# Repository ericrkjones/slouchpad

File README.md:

# slouchpad
A simple joypad for easy assembly in different types of enclosures.  

The joypad is broken into four main components:  
* Left pad, containing one joystick, d-pad, the select button, the menu buttor
* Right pad, containing one joystick, six primary buttons, and the start button
* Two shoulder pads, each containing two buttons.  

Signal List:
* 5 analog signals
* 13 digital signals
* VCC
* GND

## Hardware
Hardware designs are located in the "slouchpad_pcb" directory.
### Components
* Buttons
  * The buttons on all the pads are the Soft Tactile Buttons distributed by Adafruit Industries:
    * [Soft Tactile Button (8mm)](https://www.adafruit.com/products/3101)
  * These buttons provide the feel of a conductive silicone pad button without the expense and difficulty of producing the silicone parts.
* Joysticks
  * Joysticks are Mini 2-Axis Analog Thumbsticks distributed by Adafruit Industries:
    * [Mini 2-Axis Analog Thumbstick](https://www.adafruit.com/products/2765)
  * These joysticks have a feel that is very similar to a PSP joystick, but are available in a through-hole package.  

## License Information
The slouchpad hardware is released under [Creative Commons ShareAlike 4.0 International](https://creativecommons.org/licenses/by-sa/4.0/).  

The Mini Analog Thumbstick part layout was obtained from the [Adafruit-Mini-Analog-Thumbstick-Breakout-PCB](https://github.com/adafruit/Adafruit-Mini-Analog-Thumbstick-Breakout-PCB), designed by Ladyada for Adafruit Industries and released under the [Creative Commons Attribution-ShareAlike license](https://creativecommons.org/licenses/by-sa/3.0/).  Adafruit invests time and resources providing this open source design, please support Adafruit and open-source hardware by purchasing products from Adafruit!

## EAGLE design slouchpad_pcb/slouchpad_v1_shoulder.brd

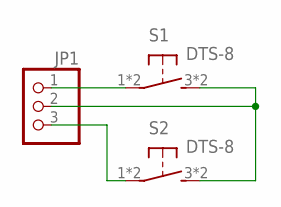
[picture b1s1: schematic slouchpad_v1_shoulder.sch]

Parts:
JP1: PINHD-1X3; 1X03
S1, S2: DTS-8

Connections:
GND: JP1.2, S1.3 (2), S1.4 (2), S2.3 (2), S2.4 (2)
S1: JP1.1, S1.1, S1.2 (1)
S2: JP1.3, S2.1, S2.2 (1)

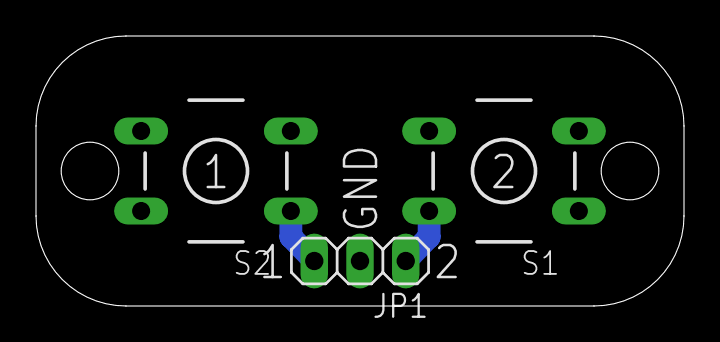
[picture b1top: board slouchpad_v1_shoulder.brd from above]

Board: 2 copper layers, 36.0 x 15.0 mm, 3 parts (0 on the bottom side), 3 nets.

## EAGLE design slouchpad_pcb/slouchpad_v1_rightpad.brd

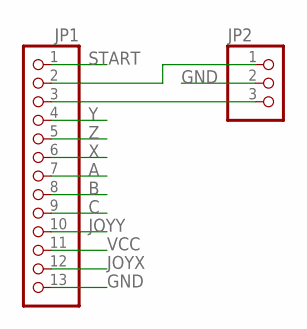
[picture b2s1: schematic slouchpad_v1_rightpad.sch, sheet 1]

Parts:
JP1: PINHD-1X13; 1X13
JP2: PINHD-1X3; 1X03

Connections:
A: JP1.7; also elsewhere on the board
B: JP1.8; also elsewhere on the board
C: JP1.9; also elsewhere on the board
GND: JP1.13, JP2.2; also elsewhere on the board
JOYX: JP1.12; also elsewhere on the board
JOYY: JP1.10; also elsewhere on the board
unnamed: JP1.2, JP2.1
unnamed: JP1.3, JP2.3
START: JP1.1; also elsewhere on the board
VCC: JP1.11; also elsewhere on the board
X: JP1.6; also elsewhere on the board
Y: JP1.4; also elsewhere on the board
Z: JP1.5; also elsewhere on the board

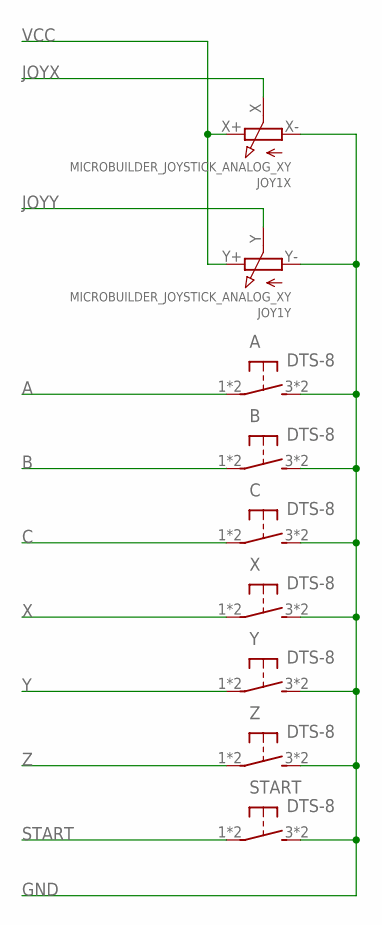
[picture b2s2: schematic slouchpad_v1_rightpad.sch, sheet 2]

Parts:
A: DTS-8
B: DTS-8
C: DTS-8
JOY1: MICROBUILDER_JOYSTICK_ANALOG_XY; MICROBUILDER_JOYSTICK_ANALOG_MINITHM
START: DTS-8
X: DTS-8
Y: DTS-8
Z: DTS-8

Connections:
A: A.1, A.2 (1); also elsewhere on the board
B: B.1, B.2 (1); also elsewhere on the board
C: C.1, C.2 (1); also elsewhere on the board
GND: A.3 (2), A.4 (2), B.3 (2), B.4 (2), C.3 (2), C.4 (2), JOY1.X- (A), JOY1.Y- (A), START.3 (2), START.4 (2), X.3 (2), X.4 (2), Y.3 (2), Y.4 (2), Z.3 (2), Z.4 (2); also elsewhere on the board
JOYX: JOY1.X (S); also elsewhere on the board
JOYY: JOY1.Y (S); also elsewhere on the board
START: START.1, START.2 (1); also elsewhere on the board
VCC: JOY1.X+ (E), JOY1.Y+ (E); also elsewhere on the board
X: X.1, X.2 (1); also elsewhere on the board
Y: Y.1, Y.2 (1); also elsewhere on the board
Z: Z.1, Z.2 (1); also elsewhere on the board

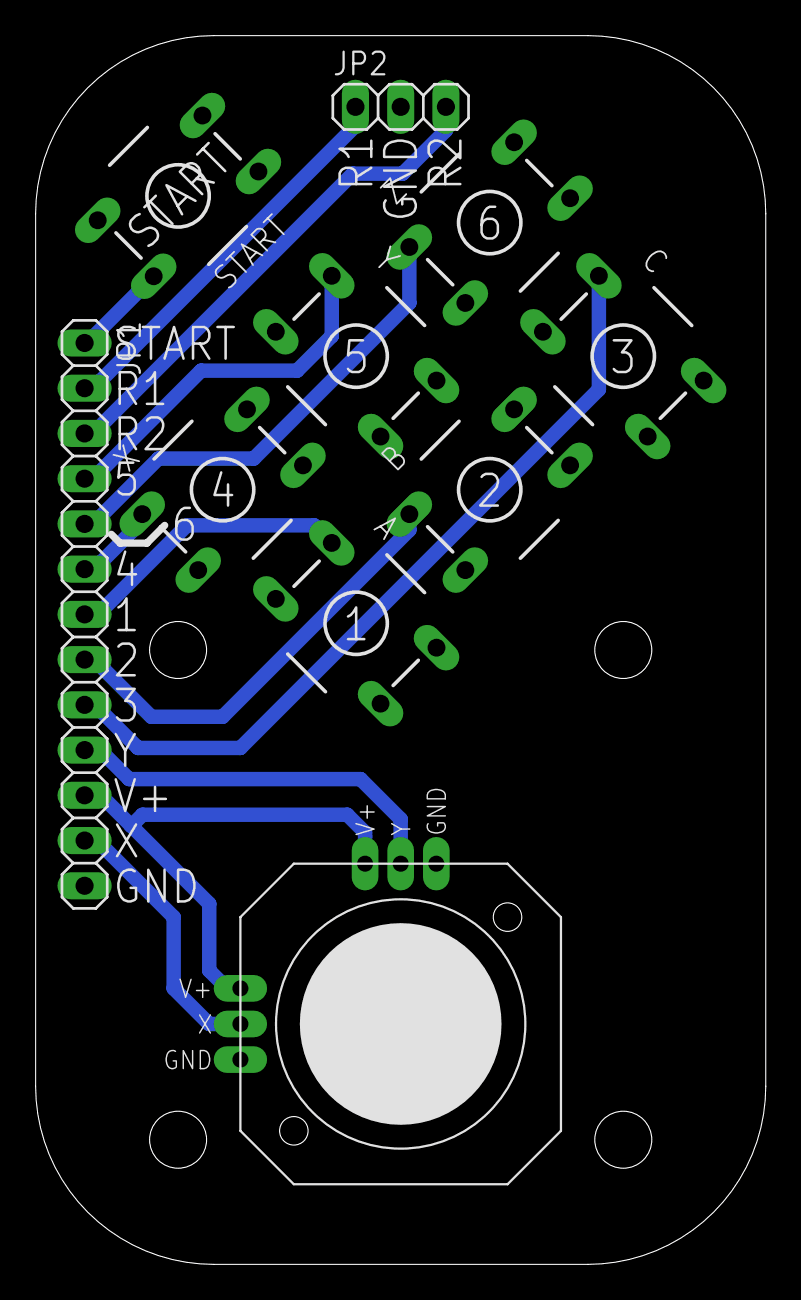
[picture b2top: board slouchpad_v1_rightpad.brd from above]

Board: 2 copper layers, 41.0 x 69.0 mm, 10 parts (0 on the bottom side), 13 nets.

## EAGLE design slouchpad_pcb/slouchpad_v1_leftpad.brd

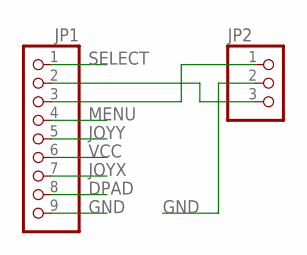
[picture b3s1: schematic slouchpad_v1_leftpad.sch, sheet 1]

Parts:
JP1: PINHD-1X9; 1X09
JP2: PINHD-1X3; 1X03

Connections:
DPAD: JP1.8; also elsewhere on the board
GND: JP1.9, JP2.2; also elsewhere on the board
JOYX: JP1.7; also elsewhere on the board
JOYY: JP1.5; also elsewhere on the board
MENU: JP1.4; also elsewhere on the board
unnamed: JP1.2, JP2.3
unnamed: JP1.3, JP2.1
SELECT: JP1.1; also elsewhere on the board
VCC: JP1.6; also elsewhere on the board

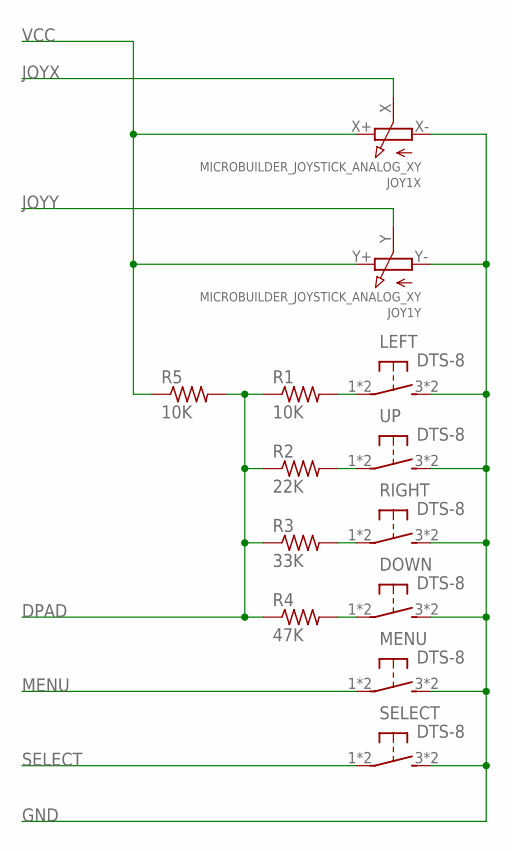
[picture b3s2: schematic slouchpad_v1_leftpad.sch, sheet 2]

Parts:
DOWN: DTS-8
JOY1: MICROBUILDER_JOYSTICK_ANALOG_XY; MICROBUILDER_JOYSTICK_ANALOG_MINITHM
LEFT: DTS-8
MENU: DTS-8
R1, R5: 10K; 0204/5
R2: 22K; 0204/5
R3: 33K; 0204/5
R4: 47K; 0204/5
RIGHT: DTS-8
SELECT: DTS-8
UP: DTS-8

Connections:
DPAD: R1.1, R2.1, R3.1, R4.1, R5.2; also elsewhere on the board
GND: DOWN.3 (2), DOWN.4 (2), JOY1.X- (A), JOY1.Y- (A), LEFT.3 (2), LEFT.4 (2), MENU.3 (2), MENU.4 (2), RIGHT.3 (2), RIGHT.4 (2), SELECT.3 (2), SELECT.4 (2), UP.3 (2), UP.4 (2); also elsewhere on the board
JOYX: JOY1.X (S); also elsewhere on the board
JOYY: JOY1.Y (S); also elsewhere on the board
MENU: MENU.1, MENU.2 (1); also elsewhere on the board
unnamed: LEFT.1, LEFT.2 (1), R1.2
unnamed: R3.2, RIGHT.1, RIGHT.2 (1)
unnamed: DOWN.1, DOWN.2 (1), R4.2
unnamed: R2.2, UP.1, UP.2 (1)
SELECT: SELECT.1, SELECT.2 (1); also elsewhere on the board
VCC: JOY1.X+ (E), JOY1.Y+ (E), R5.1; also elsewhere on the board

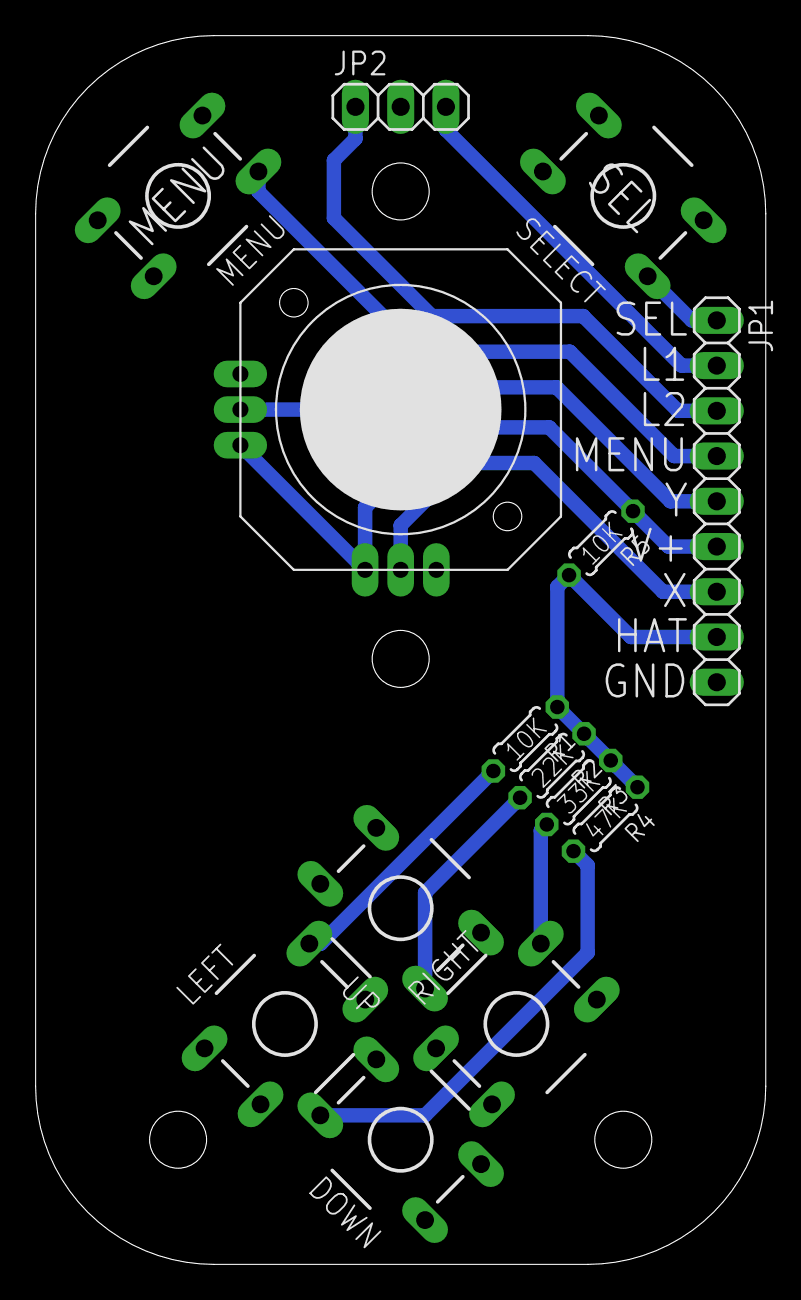
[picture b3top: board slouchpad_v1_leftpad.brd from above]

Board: 2 copper layers, 41.0 x 69.0 mm, 14 parts (0 on the bottom side), 13 nets.

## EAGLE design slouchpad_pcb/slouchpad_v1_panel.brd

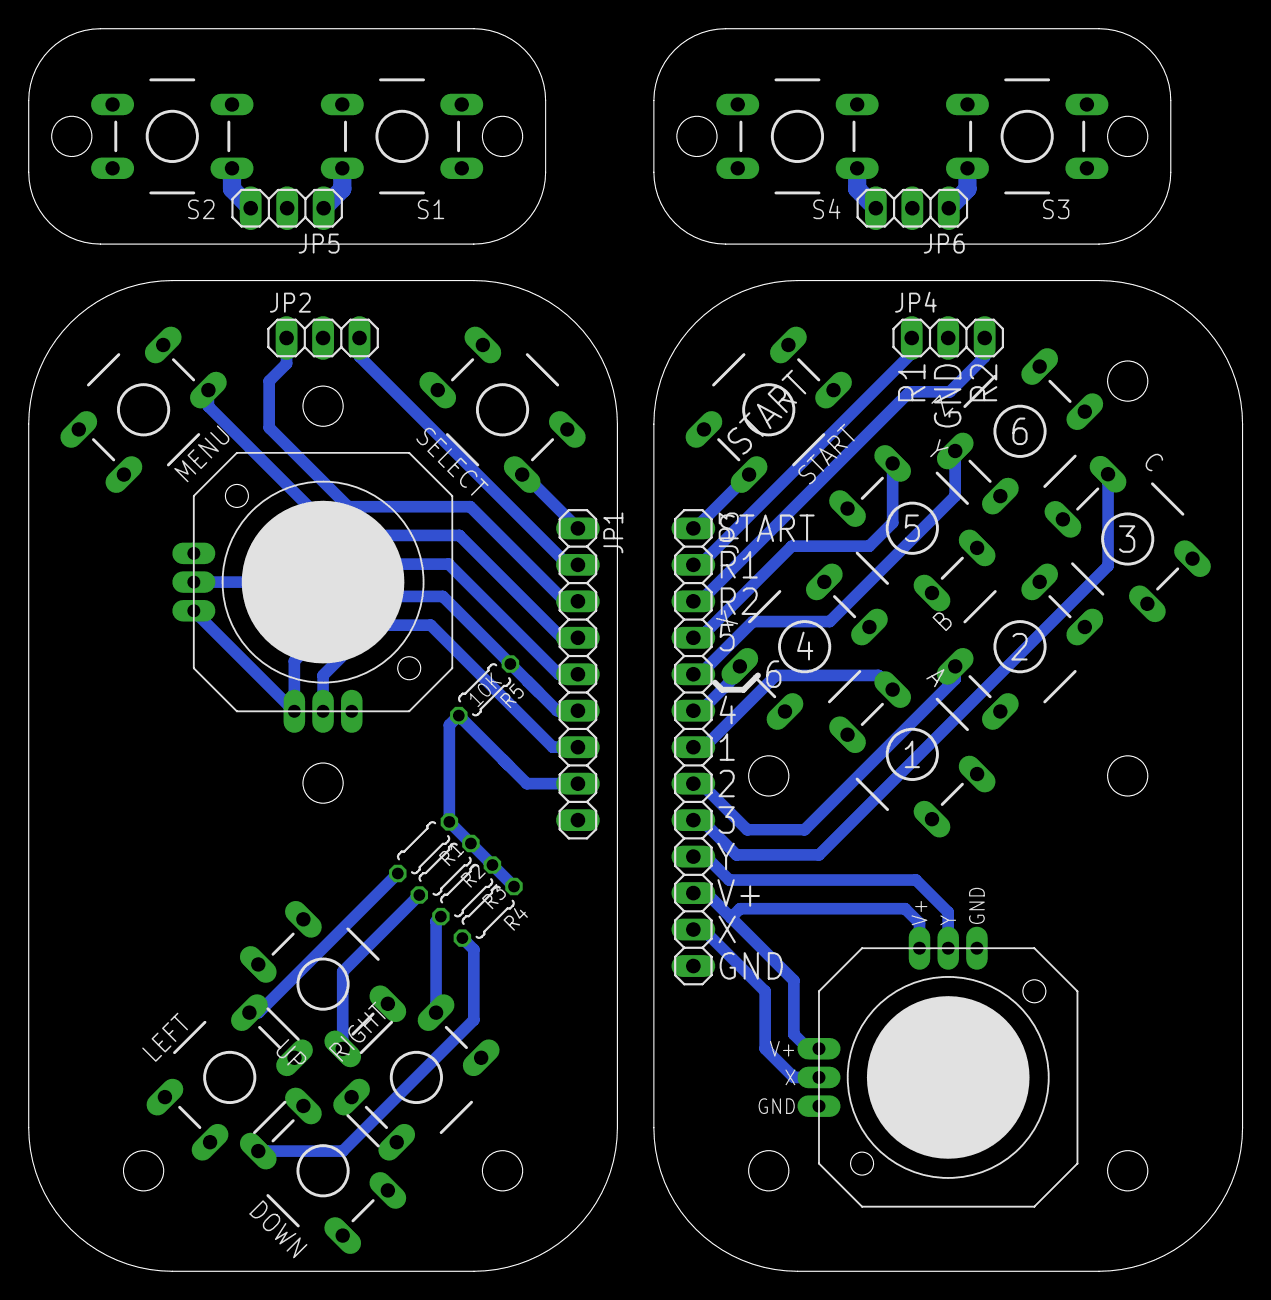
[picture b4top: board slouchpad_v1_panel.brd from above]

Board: 2 copper layers, 84.5 x 86.5 mm, 30 parts (0 on the bottom side), 32 nets.

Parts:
A: DTS-8
B: DTS-8
C: DTS-8
DOWN: DTS-8
JOY1, JOY2: MICROBUILDER_JOYSTICK_ANALOG_XY; MICROBUILDER_JOYSTICK_ANALOG_MINITHM
JP1: 1X09
JP2, JP4, JP5, JP6: 1X03
JP3: 1X13
LEFT: DTS-8
MENU: DTS-8
R1, R5: 10K; 0204/5
R2: 22K; 0204/5
R3: 33K; 0204/5
R4: 47K; 0204/5
RIGHT: DTS-8
S1, S2, S3, S4: DTS-8
SELECT: DTS-8
START: DTS-8
UP: DTS-8
X: DTS-8
Y: DTS-8
Z: DTS-8

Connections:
A: A.1, A.2, JP3.7
B: B.1, B.2, JP3.8
C: C.1, C.2, JP3.9
DPAD: JP1.8, R1.1, R2.1, R3.1, R4.1, R5.2
GND: DOWN.3, DOWN.4, JOY1.X-, JOY1.Y-, JP1.9, JP2.2, LEFT.3, LEFT.4, MENU.3, MENU.4, RIGHT.3, RIGHT.4, SELECT.3, SELECT.4, UP.3, UP.4
GND1: A.3, A.4, B.3, B.4, C.3, C.4, JOY2.X-, JOY2.Y-, JP3.13, JP4.2, START.3, START.4, X.3, X.4, Y.3, Y.4, Z.3, Z.4
GND2: JP5.2, S1.3, S1.4, S2.3, S2.4
GND3: JP6.2, S3.3, S3.4, S4.3, S4.4
JOYX: JOY1.X, JP1.7
JOYX1: JOY2.X, JP3.12
JOYY: JOY1.Y, JP1.5
JOYY1: JOY2.Y, JP3.10
MENU: JP1.4, MENU.1, MENU.2
unnamed: JP1.2, JP2.3
unnamed: JP1.3, JP2.1
unnamed: LEFT.1, LEFT.2, R1.2
unnamed: R3.2, RIGHT.1, RIGHT.2
unnamed: DOWN.1, DOWN.2, R4.2
unnamed: R2.2, UP.1, UP.2
unnamed: JP3.2, JP4.1
unnamed: JP3.3, JP4.3
S1: JP5.1, S1.1, S1.2
S2: JP5.3, S2.1, S2.2
S3: JP6.1, S3.1, S3.2
S4: JP6.3, S4.1, S4.2
SELECT: JP1.1, SELECT.1, SELECT.2
START: JP3.1, START.1, START.2
VCC: JOY1.X+, JOY1.Y+, JP1.6, R5.1
VCC1: JOY2.X+, JOY2.Y+, JP3.11
X: JP3.6, X.1, X.2
Y: JP3.4, Y.1, Y.2
Z: JP3.5, Z.1, Z.2

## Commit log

2017-03-14 Added partial eagle files via upload
    Eagle project "slouchpad_pcb" contains schematics and boards for pads and triggers. The "rightpad" and "shoulder" boards are the only ones that are fully completed. The "leftpad" file is still in dev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
2017-03-14 Delete LICENSE
    Removed MIT License to comply with terms of Creative Commons ShareAlike 4.0 International, inherited from SparkFun Arduino Pro Micro project.
2017-03-14 Update README.md
    Modified License Information to specify the use of the Creative Commons ShareAlike 4.0 International to comply with the terms of that license inherited from the SparkFun Arduino Pro Micro.
2017-03-14 Update README.md
    Updated to reflect proper licensing information for part resources.
2017-03-15 Retooled the project to be a modular joypad
    Rather than being a shield for the SparkFun Pro Micro Arduino, the slouchpad will simply be a modular joypad for use with any microcontroller.
    Modified the license to reflect the removal of the SparkFun Pro Micro
    Removed backup design files
    Created button layout for left thumb pad
    Modified all board positions to units of mm where possible.
2017-03-15 Finished board layouts
    Cleaned up schematics
2017-03-17 Finished silkscreen of boards
    Moved traces to bottom layer to represent design intention
2017-08-01 Added dimensions to baord drawings and fixed button 5 position to have correct spacing.
